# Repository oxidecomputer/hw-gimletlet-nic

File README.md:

# hw-gimletlet-nic
Daughterboard for the Gimletlet 2 which uses a KSZ8463 to break out two ethernet (RJ-45) connectors. In active use for Hubris development.

Some [Design Notes](docs/DesignNotes.md)

# Status
In active use, no required rework.

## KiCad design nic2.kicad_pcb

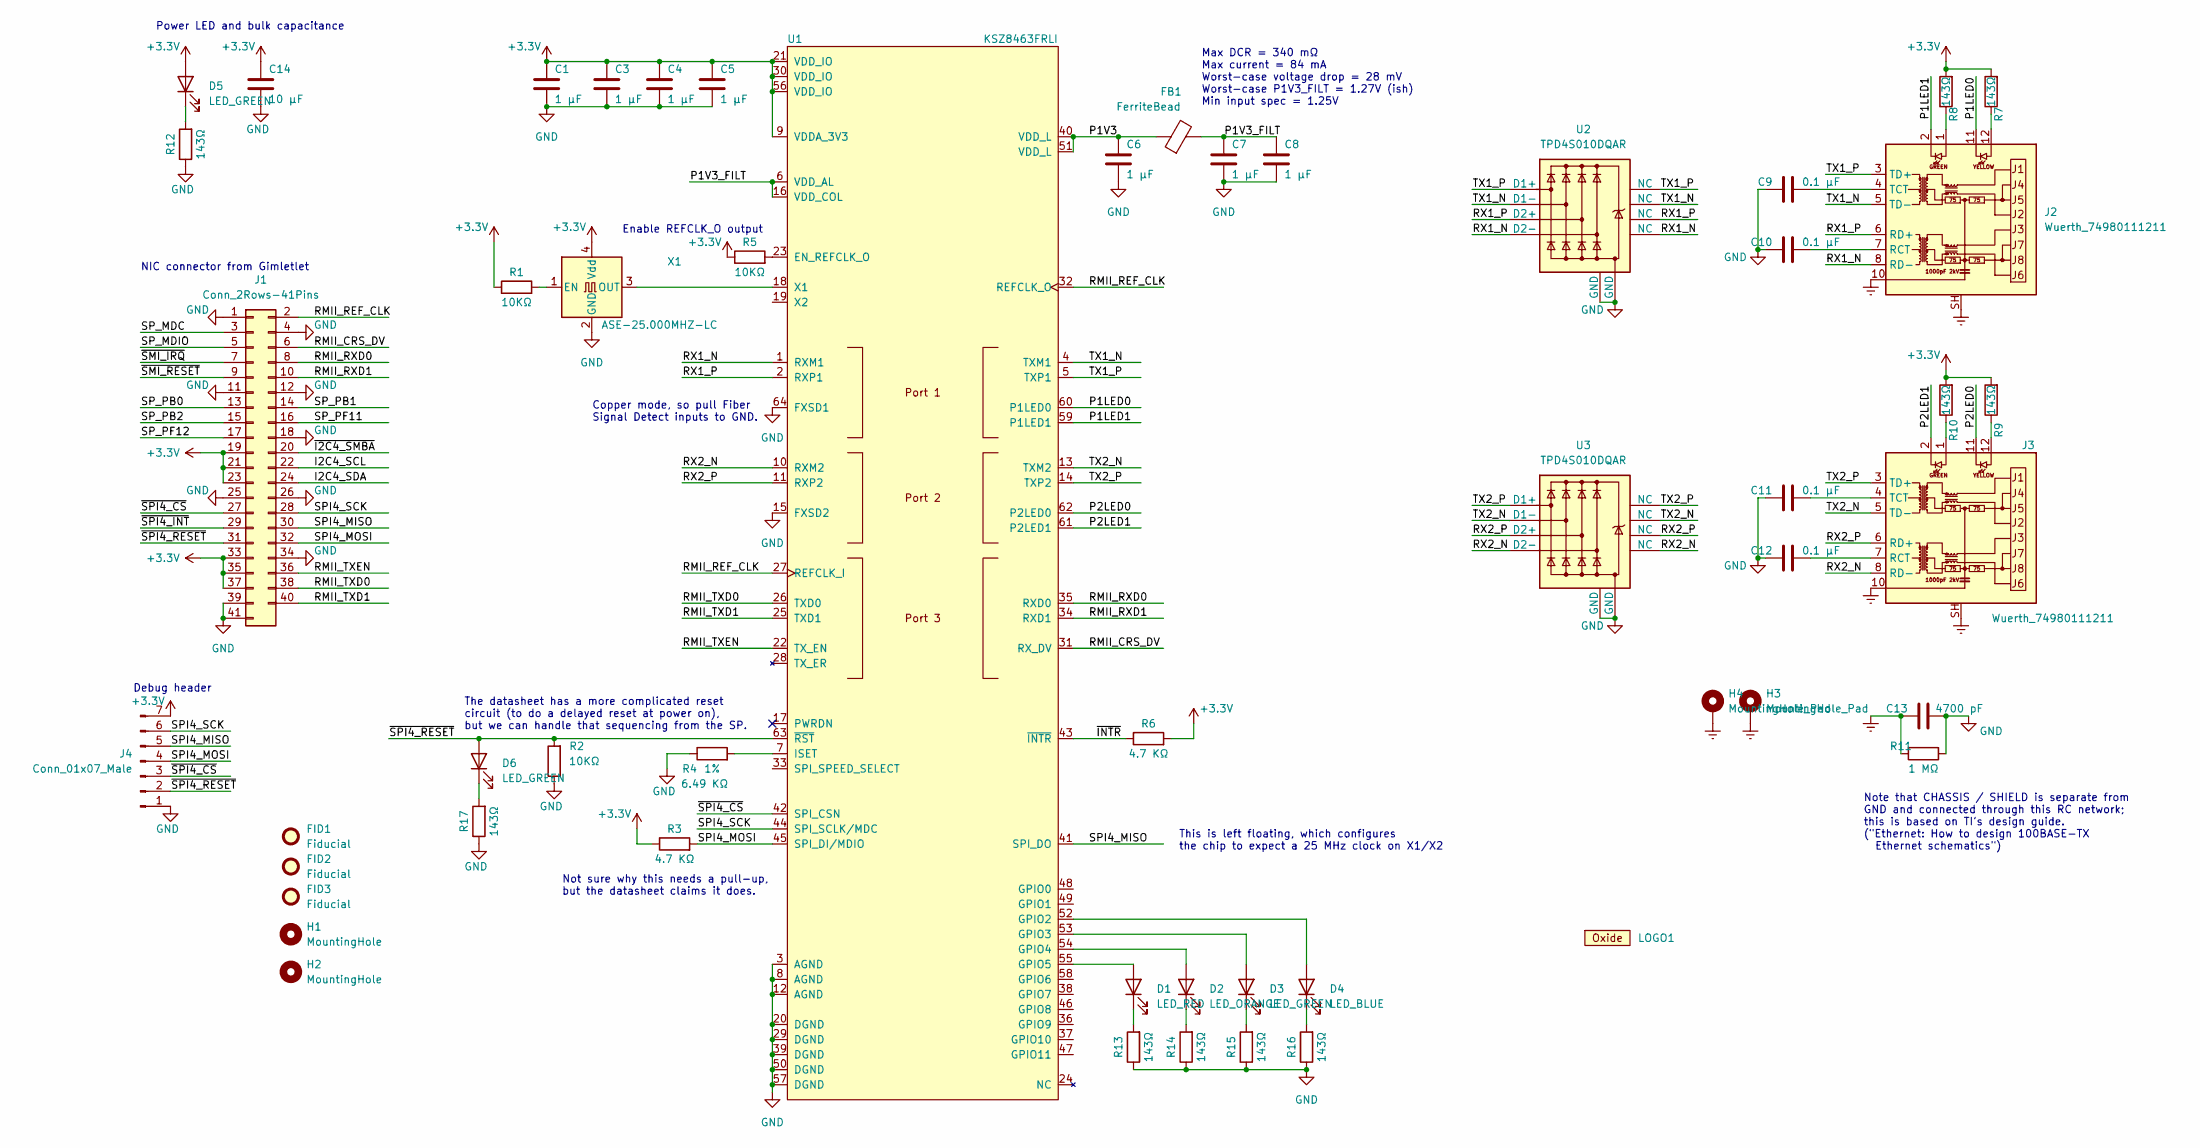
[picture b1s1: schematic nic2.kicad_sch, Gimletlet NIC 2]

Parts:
C1, C3, C4, C5, C6, C7, C8: 1 µF; C_0402_1005Metric; MPN C0402C105K9PAC7800
C9, C10, C11, C12: 0.1 µF; C_0402_1005Metric; MPN C0402C104K9RAC7867
C13: 4700 pF; C_0402_1005Metric; MPN C0402C472K3RAC7867
C14: 10 µF; C_0805_2012Metric; MPN C0805C106K9RAC7800
D1: LED_RED; LED_0402_1005Metric; MPN XZMDK68W-2
D2: LED_ORANGE; LED_0402_1005Metric; MPN XZMOK68W-2
D3, D5, D6: LED_GREEN; LED_0402_1005Metric; MPN XZVG68W-2
D4: LED_BLUE; LED_0402_1005Metric; MPN VLMB1500-GS08
FB1: FerriteBead; R_0402_1005Metric; MPN BLM15AX601SN1D
FID1, FID2, FID3: Fiducial; Fiducial_0.75mm_Mask1.5mm
H1, H2: MountingHole; MountingHole_3.2mm_M3
H3, H4: MountingHole_Pad; MountingHole_3.2mm_M3_DIN965_Pad
J1: Conn_2Rows-41Pins; DF9-41P-1V; MPN DF9-41P-1V(69)
J2, J3: Wuerth_74980111211; RJ45_Wuerth_74980111211_Horizontal; MPN 74980111211
J4: Conn_01x07_Male; PinHeader_1x07_P2.54mm_Vertical
LOGO1: LOGO; OXIDE_Wordmark
R1, R2, R5: 10KΩ; R_0402_1005Metric; MPN CRG0402F10K
R3, R6: 4.7 KΩ; R_0402_1005Metric; MPN CRG0402F4K7
R4: 6.49 KΩ; R_0402_1005Metric; MPN RC0402FR-076K49L
R7, R8, R9, R10, R12, R13, R14, R15, R16, R17: 143Ω; R_0402_1005Metric; MPN RC0402FR-07143RL
R11: 1 MΩ; R_0402_1005Metric; MPN CRG0402F1M0
U1: KSZ8463FRLI; LQFP-64_10x10mm_P0.5mm; MPN KSZ8463FRLI
U2, U3: TPD4S010DQAR; USON-10_2.5x1.0mm_P0.5mm; MPN TPD4S010DQAR
X1: ASE-25.000MHZ-LC; Oscillator_SMD_Abracon_ASE-4Pin_3.2x2.5mm; MPN ASE-25.000MHZ-LC-T

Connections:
+3V3: C1.2, C3.2, C4.2, C5.2, C14.2, D5.2 (A), J1.19, J1.21, J1.23, J1.33, J1.35, J1.37, J4.7, R1.1, R3.1, R5.1, R6.2, R7.2, R8.2, R9.2, R10.2, U1.9 (VDDA_3V3), U1.21 (VDD_IO), U1.30 (VDD_IO), U1.56 (VDD_IO), X1.4 (Vdd)
/I2C4_SCL: J1.22
/I2C4_SDA: J1.24
/P1LED0: J2.11, U1.60 (P1LED0)
/P1LED1: J2.2, U1.59 (P1LED1)
/P1V3: C6.2, FB1.1, U1.40 (VDD_L), U1.51 (VDD_L)
/P1V3_FILT: C7.2, C8.2, FB1.2, U1.6 (VDD_AL), U1.16 (VDD_COL)
/P2LED0: J3.11, U1.62 (P2LED0)
/P2LED1: J3.2, U1.61 (P2LED1)
/RMII_CRS_DV: J1.6, U1.31 (RX_DV)
/RMII_REF_CLK: J1.2, U1.27 (REFCLK_I), U1.32 (REFCLK_O)
/RMII_RXD0: J1.8, U1.35 (RXD0)
/RMII_RXD1: J1.10, U1.34 (RXD1)
/RMII_TXD0: J1.38, U1.26 (TXD0)
/RMII_TXD1: J1.40, U1.25 (TXD1)
/RMII_TXEN: J1.36, U1.22 (TX_EN)
/RX1_N: J2.8 (RD-), U1.1 (RXM1), U2.5 (D2-), U2.6 (NC)
/RX1_P: J2.6 (RD+), U1.2 (RXP1), U2.4 (D2+), U2.7 (NC)
/RX2_N: J3.8 (RD-), U1.10 (RXM2), U3.5 (D2-), U3.6 (NC)
/RX2_P: J3.6 (RD+), U1.11 (RXP2), U3.4 (D2+), U3.7 (NC)
/SPI4_MISO: J1.30, J4.5, U1.41 (SPI_DO)
/SPI4_MOSI: J1.32, J4.4, R3.2, U1.45 (SPI_DI/MDIO)
/SPI4_SCK: J1.28, J4.6, U1.44 (SPI_SCLK/MDC)
/SP_MDC: J1.3
/SP_MDIO: J1.5
/SP_PB0: J1.13
/SP_PB1: J1.14
/SP_PB2: J1.15
/SP_PF11: J1.16
/SP_PF12: J1.17
/TX1_N: J2.5 (TD-), U1.4 (TXM1), U2.2 (D1-), U2.9 (NC)
/TX1_P: J2.3 (TD+), U1.5 (TXP1), U2.1 (D1+), U2.10 (NC)
/TX2_N: J3.5 (TD-), U1.13 (TXM2), U3.2 (D1-), U3.9 (NC)
/TX2_P: J3.3 (TD+), U1.14 (TXP2), U3.1 (D1+), U3.10 (NC)
/~I2C4_SMBA: J1.20
/~INTR: R6.1, U1.43 (~INTR)
/~SMI_IRQ: J1.7
/~SMI_RESET: J1.9
/~SPI4_CS: J1.27, J4.3, U1.42 (SPI_CSN)
/~SPI4_INT: J1.29
/~SPI4_RESET: D6.2 (A), J1.31, J4.2, R2.2, U1.63 (~RST)
Earth: C13.2, H3.1, H4.1, J2.10, J2.SH, J3.10, J3.SH, R11.2
GND: C1.1, C3.1, C4.1, C5.1, C6.1, C7.1, C8.1, C9.2, C10.2, C11.2, C12.2, C13.1, C14.1, J1.1, J1.4, J1.11, J1.12, J1.18, J1.25, J1.26, J1.34, J1.39, J1.41, J4.1, R2.1, R4.1, R11.1, R12.1, R13.1, R14.1, R15.1, R16.1, R17.1, U1.3 (AGND), U1.8 (AGND), U1.12 (AGND), U1.15 (FXSD2), U1.20 (DGND), U1.29 (DGND), U1.39 (DGND), U1.50 (DGND), U1.57 (DGND), U1.64 (FXSD1), U2.3 (GND), U2.8 (GND), U3.3 (GND), U3.8 (GND), X1.2 (GND)
unnamed: C9.1, J2.4 (TCT)
unnamed: C10.1, J2.7 (RCT)
unnamed: C11.1, J3.4 (TCT)
unnamed: C12.1, J3.7 (RCT)
unnamed: D1.1 (K), R13.2
unnamed: D1.2 (A), U1.55 (GPIO5)
unnamed: D2.1 (K), R14.2
unnamed: D2.2 (A), U1.54 (GPIO4)
unnamed: D3.1 (K), R15.2
unnamed: D3.2 (A), U1.53 (GPIO3)
unnamed: D4.1 (K), R16.2
unnamed: D4.2 (A), U1.52 (GPIO2)
unnamed: D5.1 (K), R12.2
unnamed: D6.1 (K), R17.2
unnamed: J2.1, R8.1
unnamed: J2.12, R7.1
unnamed: J3.1, R10.1
unnamed: J3.12, R9.1
unnamed: R1.2, X1.1 (EN)
unnamed: R4.2, U1.7 (ISET)
unnamed: R5.2, U1.23 (EN_REFCLK_O)
unnamed: U1.18 (X1), X1.3 (OUT)

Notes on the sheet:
Note that CHASSIS / SHIELD is separate from GND and connected through this RC network; this is based on TI's design guide. ("Ethernet: How to design 100BASE-TX Ethernet schematics")
Enable REFCLK_O output
The datasheet has a more complicated reset circuit (to do a delayed reset at power on), but we can handle that sequencing from the SP.
Not sure why this needs a pull-up, but the datasheet claims it does.
Debug header
Copper mode, so pull Fiber Signal Detect inputs to GND.
Max DCR = 340 mΩ Max current = 84 mA Worst-case voltage drop = 28 mV Worst-case P1V3_FILT = 1.27V (ish) Min input spec = 1.25V
This is left floating, which configures the chip to expect a 25 MHz clock on X1/X2
NIC connector from Gimletlet
Power LED and bulk capacitance

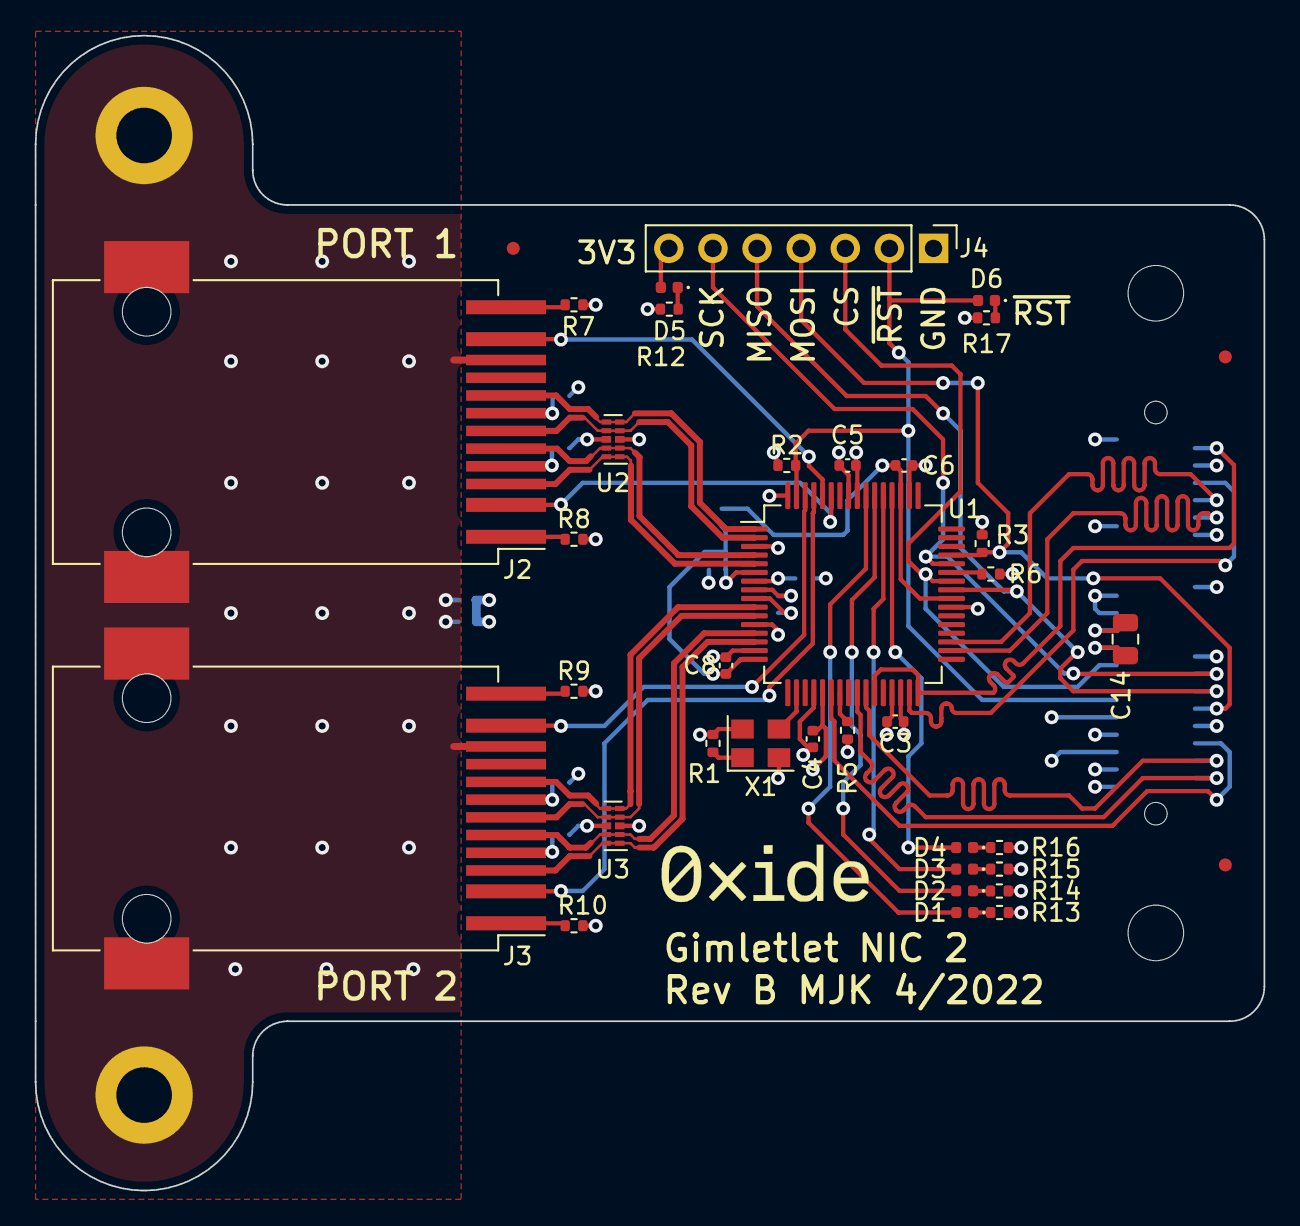
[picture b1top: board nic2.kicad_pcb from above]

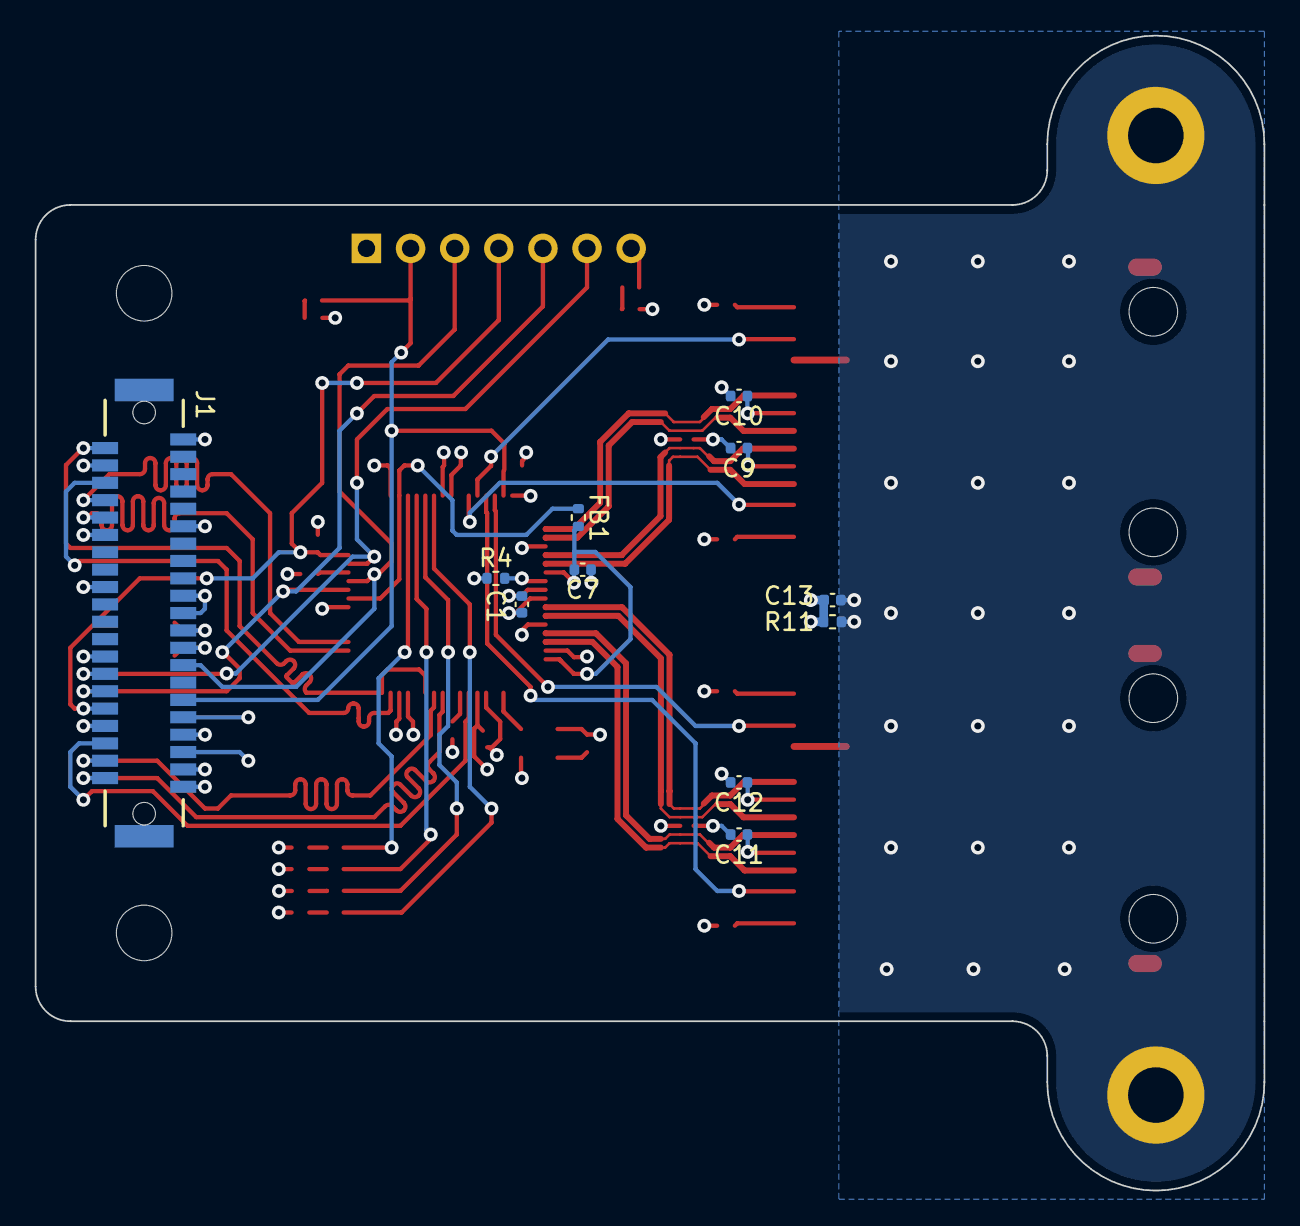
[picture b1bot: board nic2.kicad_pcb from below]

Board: 4 copper layers, 70.8 x 66.5 mm, 53 parts (11 on the bottom side), 52 nets.

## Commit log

2023-02-28 Move out of gemini repo
2023-02-28 fix paths
